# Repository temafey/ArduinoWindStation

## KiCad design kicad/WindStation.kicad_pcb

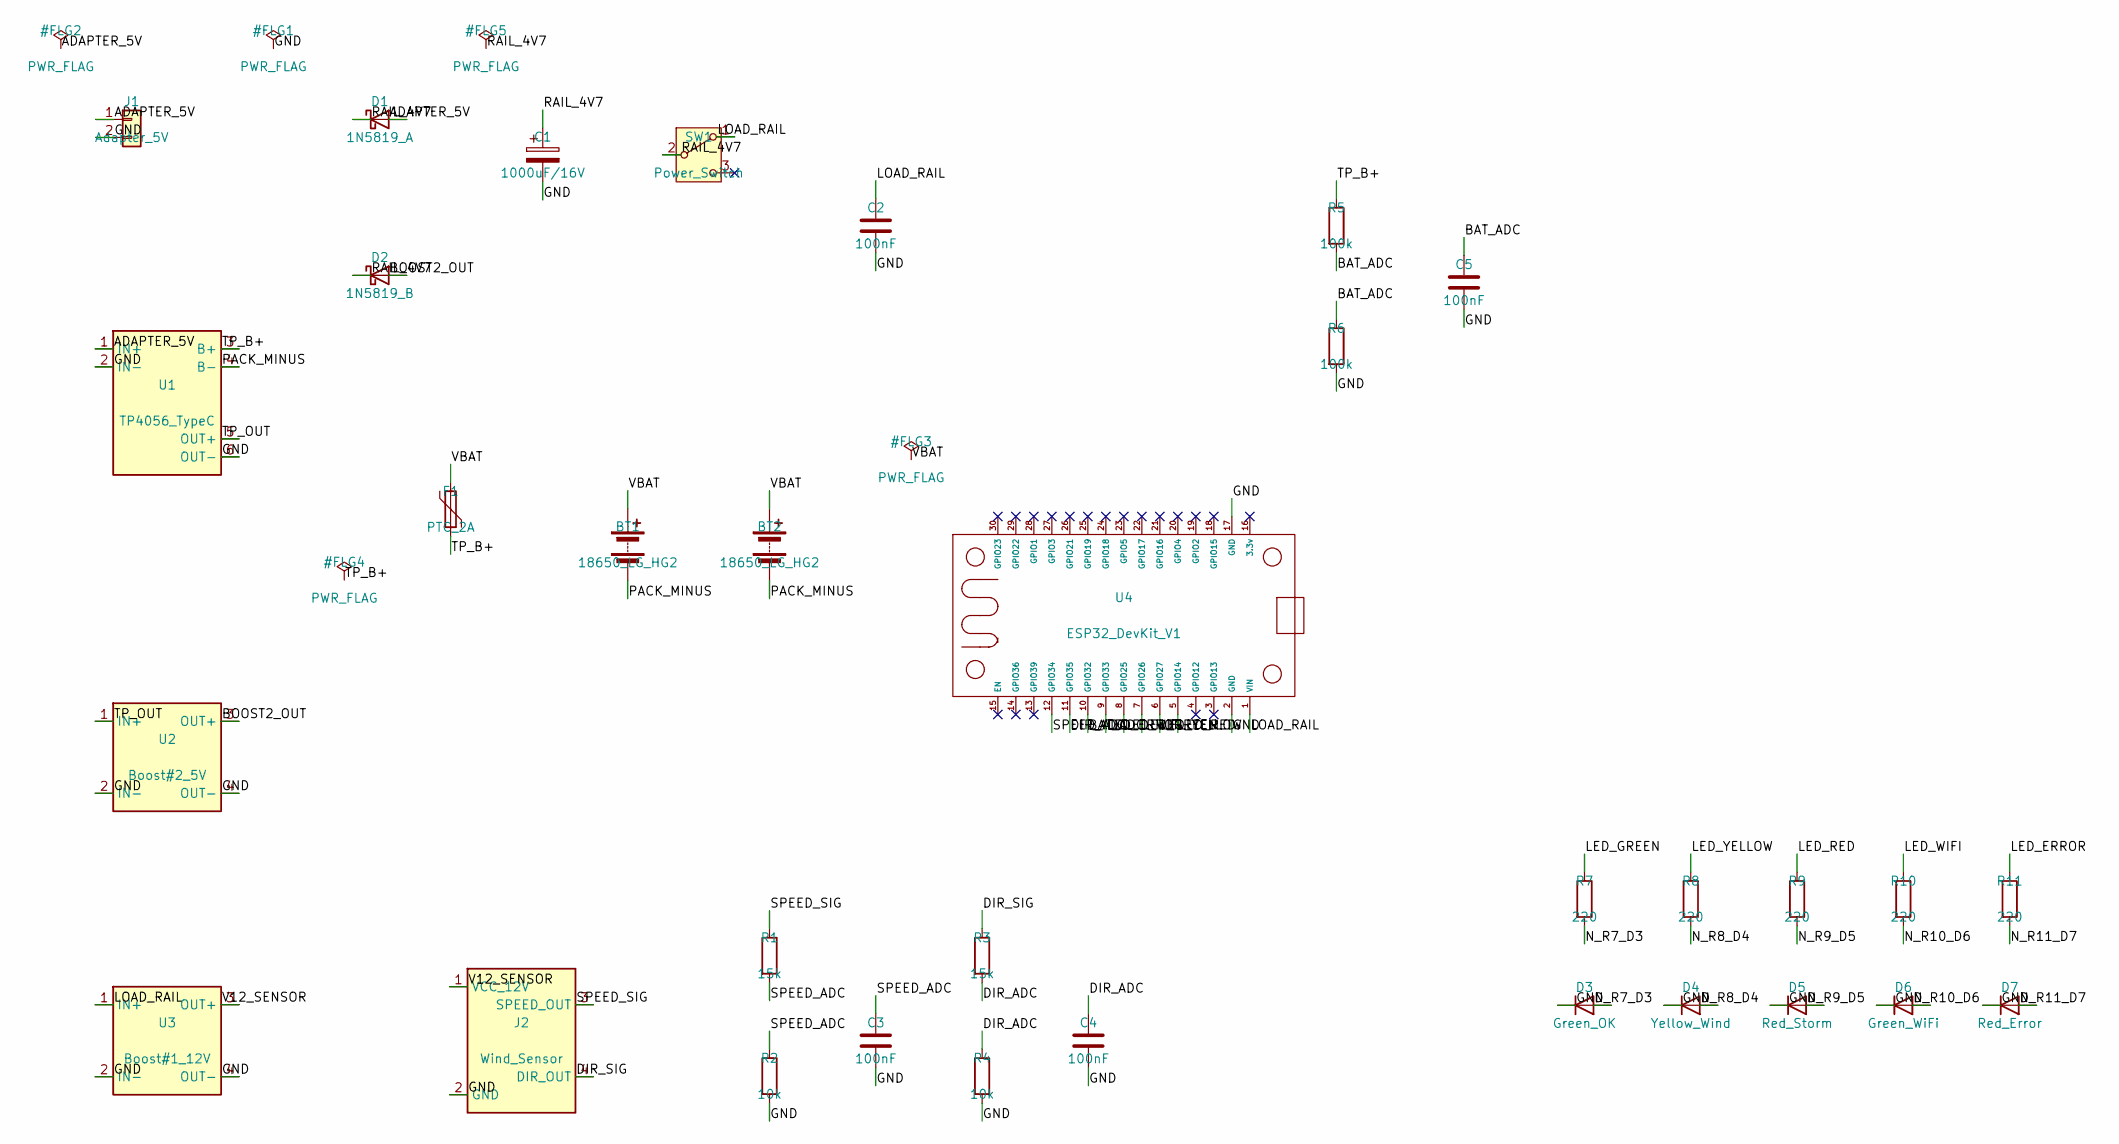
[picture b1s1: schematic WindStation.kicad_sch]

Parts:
BT1, BT2: 18650_LG_HG2; BatteryHolder_Keystone_1042_1x18650
C1: 1000uF/16V; CP_Radial_D10.0mm_P5.00mm
C2, C3, C4, C5: 100nF; C_Disc_D5.0mm_W2.5mm_P5.00mm
D1: 1N5819_A; D_DO-41_SOD81_P10.16mm_Horizontal
D2: 1N5819_B; D_DO-41_SOD81_P10.16mm_Horizontal
D3: Green_OK; LED_D5.0mm
D4: Yellow_Wind; LED_D5.0mm
D5: Red_Storm; LED_D5.0mm
D6: Green_WiFi; LED_D5.0mm
D7: Red_Error; LED_D5.0mm
F1: PTC_2A; Fuse_Bourns_MF-RG400
J1: Adapter_5V; PinHeader_1x02_P2.54mm_Vertical
J2: Wind_Sensor; PinHeader_1x04_P2.54mm_Vertical
R1, R3: 15k; R_Axial_DIN0207_L6.3mm_D2.5mm_P10.16mm_Horizontal
R2, R4: 10k; R_Axial_DIN0207_L6.3mm_D2.5mm_P10.16mm_Horizontal
R5, R6: 100k; R_Axial_DIN0207_L6.3mm_D2.5mm_P10.16mm_Horizontal
R7, R8, R9, R10, R11: 220; R_Axial_DIN0207_L6.3mm_D2.5mm_P10.16mm_Horizontal
SW1: Power_Switch; PinHeader_1x03_P2.54mm_Vertical
U1: TP4056_TypeC; PinHeader_1x06_P2.54mm_Vertical
U2: Boost#2_5V; PinHeader_1x04_P2.54mm_Vertical
U3: Boost#1_12V; PinHeader_1x04_P2.54mm_Vertical
U4: ESP32_DevKit_V1; ESP32_DevKit_V1_30pin

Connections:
/ADAPTER_5V: D1.2 (A), J1.1, U1.1 (IN+)
/BAT_ADC: C5.1, R5.2, R6.1, U4.10 (GPIO32)
/BOOST2_OUT: D2.2 (A), U2.3 (OUT+)
/DIR_ADC: C4.1, R3.2, R4.1, U4.11 (GPIO35)
/DIR_SIG: J2.4 (DIR_OUT), R3.1
/GND: C1.2, C2.2, C3.2, C4.2, C5.2, D3.1 (K), D4.1 (K), D5.1 (K), D6.1 (K), D7.1 (K), J1.2, J2.2 (GND), R2.2, R4.2, R6.2, U1.2 (IN-), U1.6 (OUT-), U2.2 (IN-), U2.4 (OUT-), U3.2 (IN-), U3.4 (OUT-), U4.2 (GND), U4.17 (GND)
/LED_ERROR: R11.1, U4.9 (GPIO33)
/LED_GREEN: R7.1, U4.7 (GPIO26)
/LED_RED: R9.1, U4.5 (GPIO14)
/LED_WIFI: R10.1, U4.8 (GPIO25)
/LED_YELLOW: R8.1, U4.6 (GPIO27)
/LOAD_RAIL: C2.1, SW1.1 (A), U3.1 (IN+), U4.1 (VIN)
/N_R7_D3: D3.2 (A), R7.2
/N_R8_D4: D4.2 (A), R8.2
/N_R9_D5: D5.2 (A), R9.2
/N_R10_D6: D6.2 (A), R10.2
/N_R11_D7: D7.2 (A), R11.2
/PACK_MINUS: BT1.2 (-), BT2.2 (-), U1.4 (B-)
/RAIL_4V7: C1.1, D1.1 (K), D2.1 (K), SW1.2 (B)
/SPEED_ADC: C3.1, R1.2, R2.1, U4.12 (GPIO34)
/SPEED_SIG: J2.3 (SPEED_OUT), R1.1
/TP_B+: F1.2, R5.1, U1.3 (B+)
/TP_OUT: U1.5 (OUT+), U2.1 (IN+)
/V12_SENSOR: J2.1 (VCC_12V), U3.3 (OUT+)
/VBAT: BT1.1 (+), BT2.1 (+), F1.1

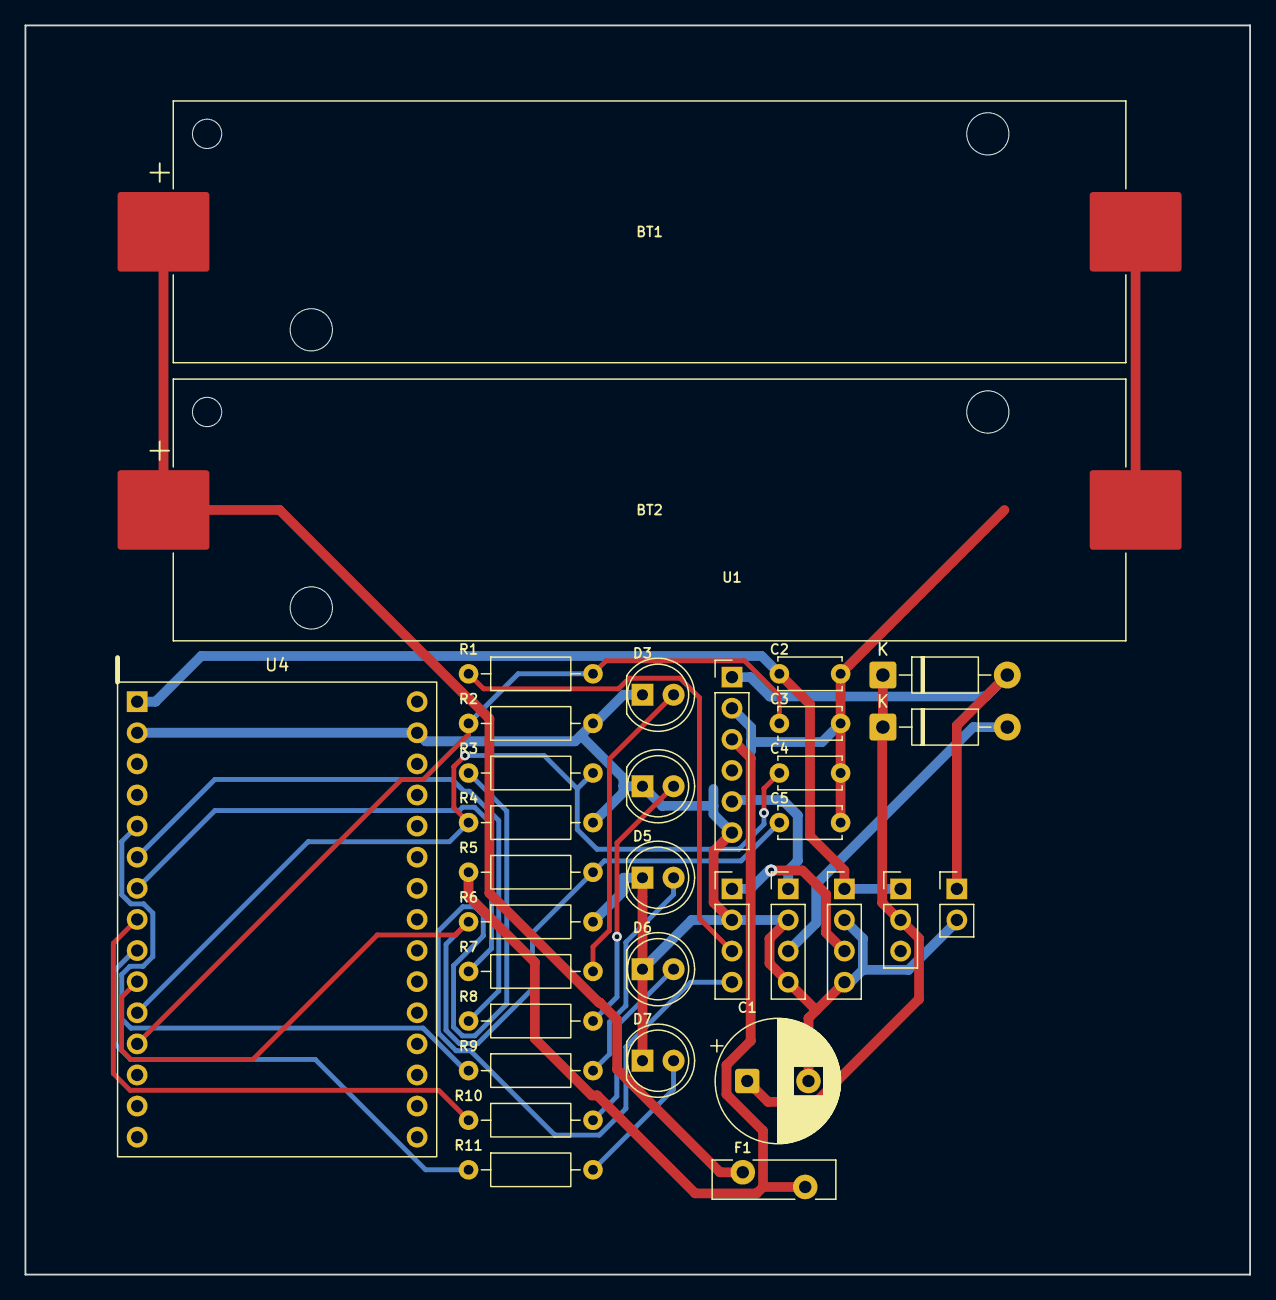
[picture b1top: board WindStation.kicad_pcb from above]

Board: 2 copper layers, 100.0 x 102.0 mm, 33 parts (0 on the bottom side), 25 nets.

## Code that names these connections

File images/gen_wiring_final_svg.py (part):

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                f"{gpio_col}a", f"{anode_col}a", "СВЕТОДИОДЫ", w=2.4, opacity=0.75)

led_wires = (
    led_wire(5, 20, LANE["led14"], bb.LED_R,   "GPIO14 → анод красного") +
    led_wire(6, 28, LANE["led27"], "#d8a017",  "GPIO27 → анод жёлтого") +
    led_wire(7, 36, LANE["led26"], bb.LED_G,   "GPIO26 → анод зелёного") +
    led_wire(8, 44, LANE["led25"], bb.LED_WIFI,"GPIO25 → анод WiFi") +
    led_wire(9, 52, LANE["led33"], "#8d8d8d",  "GPIO33 → анод ошибки"))

# ═══════════════════════════════════════════════════ 6. СИГНАЛЬНЫЕ ПРОВОДА В АЦП
# Подъём через траншею — в промежутке МЕЖДУ колонками, чтобы не путать с узлом.
sig32 = wire([H(48, "g"), (X(48)+8.5, Y("g")), (X(48)+8.5, LANE["g32"]),
              (X(10), LANE["g32"]), H(10, "a")],
             SIG, "узел X (делитель батареи) → GPIO32", "48g", "10a", "АЦП", w=3.0)
sig34 = wire([H(54, "g"), (X(54)+8.5, Y("g")), (X(54)+8.5, LANE["g34"]),
              (X(12), LANE["g34"]), H(12, "a")],
             SIG, "узел 54 (делитель скорости) → GPIO34", "54g", "12a", "АЦП", w=3.0)
sig_lbl = (f'<text x="895" y="418" font-size="9.5" font-weight="700" fill="#c47015">узел X (48g) → 32</text>'
           f'<text x="1074" y="418" font-size="9.5" font-weight="700" fill="#c47015" text-anchor="end">узел 54 (54g) → 34</text>')

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  <text x="{IX+14}" y="{IY+85}" font-size="10.5" fill="#5a4340">не выведены. <tspan font-weight="700">Проверь на плате.</tspan></text>
  <text x="{IX+14}" y="{IY+108}" font-size="11" font-weight="700" fill="#1a1a1a">Если ряд j свободен:</text>
  <text x="{IX+14}" y="{IY+124}" font-size="10.5" fill="#333">STDBY → 19j напрямую. Прошивка без правок.</text>
  <text x="{IX+14}" y="{IY+147}" font-size="11" font-weight="700" fill="#1a1a1a">Если свободен только ряд a → GPIO35:</text>
  <text x="{IX+14}" y="{IY+163}" font-size="10" fill="#666">35 свободен (направления у нового датчика нет),</text>
  <text x="{IX+14}" y="{IY+176}" font-size="10" fill="#666">но он input-only — внутренней подтяжки НЕТ.</text>
  <g stroke-linecap="round" stroke-linejoin="round" fill="none">
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  <text x="{IX+100}" y="{IY+243}" font-size="10.5" font-weight="700" fill="{bb.COPPER}">R7 10k</text>
  <text x="{IX+100}" y="{IY+295}" font-size="10.5" font-weight="700" fill="{bb.COPPER}">R8 20k</text>
  <text x="{IX+256}" y="{IY+204}" font-size="10" font-weight="700" fill="{PLUS}">LOAD</text>
  <text x="{IX+206}" y="{IY+261}" font-size="10" font-weight="700" fill="#c47015">→ GPIO35</text>
  <text x="{IX+206}" y="{IY+284}" font-size="9.5" font-weight="700" fill="#2a7de1">STDBY</text>
  <text x="{IX+136}" y="{IY+326}" font-size="10" fill="#555">«−» рельс</text>
  <text x="{IX+14}" y="{IY+345}" font-size="10" fill="#2e7d32">Покой 4.7×20/30 = <tspan font-weight="700">3.13 В</tspan> (Vih 2.48 В) · ток стока 0.47 мА.</text>
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  <text x="46" y="{NY+87}" font-size="12.5" fill="#c0392b">⚠  <tspan font-weight="700">Колонки 44, 48, 52, 56 живут дважды:</tspan> верхний банк (ряд a) — светодиоды, нижний (f–j) — питание и делители. Это РАЗНЫЕ узлы, траншея их разделяет.</text>
  <text x="46" y="{NY+108}" font-size="12.5" fill="#c0392b">⚠  <tspan font-weight="700">Термоклей поверх поля проводов — нельзя</tspan> (затекает в отверстия по капилляру, гнездо мертво). Модули — на дно, прижимной поролон — в крышку. Силикон только нейтральный.</text>
  <text x="46" y="{NY+129}" font-size="12.5" fill="#2e7d32">✓  Порядок: 1) PPTC · 2) перетыкание по колонкам, по одному проводу · 3) прозвонка 8 мостов · 4) ШИНА 4.6–4.8 В · 5) wiggle-тест каждого провода · 6) закрытие.</text>
  <text x="46" y="{NY+150}" font-size="12.5" fill="#2a6fd1">→  Направление (кол. 16–20) НЕ монтируется: у нового датчика 0–30 м/с этого канала нет. GPIO35 свободен — см. врезку про STDBY.</text>
  <text x="46" y="{NY+168}" font-size="11" fill="#999">Отступление от images/BREADBOARD-STANDARD.md §4.2 (плавные дуги) сделано сознательно: прямые углы здесь — предмет документа.</text>'''

VH = NY + 200
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
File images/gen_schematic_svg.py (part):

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    ], dark=False, tfill=INK))
    o.append(wire([(240, 182), (300, 182)], PLUS))
    o.append(dot(300, 182))
    o.append(netlabel(268, 160, "ADAPTER_5V", PLUS))
    o.append(diode_h(300, 430, 182, "D1 · 1N5819", "катод → шина"))
    o.append(wire([(430, 182), (1090, 182)], PLUS))
    # ответвление на заряд TP4056 IN+
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    o.append(wire([(290, 984), (575, 984), (575, 639)], PURPLE, 3.8))
    o.append(hop(575, 630, PURPLE, 3.8))
    o.append(wire([(575, 621), (575, TPy + TPh)], PURPLE, 3.8))
    o.append(netlabel(700, 984, "PACK_MINUS", PURPLE, anchor="start"))
    o.append(f'<text x="700" y="1008" font-size="11.5" fill="{PURPLE}">'
             f'НЕ на общий GND — иначе DW01A обойдён</text>')

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    o.append(res_v(470, 660, 790, "R6", "100k", lab_side="left"))
    o.append(dot(470, 630, SIG))
    o.append(gnd(470, 790))
    # C5 + оранжевый на GPIO32
    o.append(wire([(470, 630), (1270, 630)], SIG, 3.2))
    o.append(dot(680, 630, SIG))
    o.append(cap_v(680, 630, 700, "C5 100нФ"))
    o.append(gnd(680, 700))
    o.append(wire([(1270, 630), (1270, 400), (1360, 400)], SIG, 3.2))
    o.append(netlabel(950, 630, "BAT_ADC", SIG, volts="ждём 1.99 В и РОВНО"))
    o.append(f'<text x="790" y="612" font-size="11.5" font-weight="700" fill="#c47015">'
             f'узел X → GPIO32</text>')

    # ================= BOOST#2 =================
    o.append(wire([(650, 330), (700, 330)], PLUS))
    o.append(netlabel(675, 282, "TP_OUT", PLUS, volts="ждём 3.9 В"))
    Bx, By, Bw, Bh = 700, 262, 190, 172
    o.append(sch_mod(Bx, By, Bw, Bh, "Mini Boost · MT3608", "→ 5.14 В (задача 02 ✓)", [
        (Bx, 330, "IN+", "left", PLUS, SILK),
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
    # ================= D2 → ШИНА =================
    o.append(wire([(890, 330), (930, 330)], PLUS))
    o.append(netlabel(910, 296, "BOOST2_OUT", PLUS, volts="5.14 В"))
    o.append(diode_h(930, 1090, 330, "D2 · 1N5819", "катод → шина"))
    o.append(wire([(1090, 182), (1090, 330)], PLUS))
    o.append(dot(1090, 182)); o.append(dot(1090, 330))
    o.append(netlabel(1090, 262, "RAIL_4V7", PLUS, volts="4.6–4.8 В"))
    # C1 на шине
    o.append(wire([(1090, 330), (1090, 430)], PLUS))
    o.append(dot(1090, 400))
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    o.append(wire([(1090, 182), (1150, 182)], PLUS))
    o.append(switch_h(1150, 1270, 182, "SW1", "главный выключатель"))
    o.append(wire([(1270, 182), (1420, 182), (1420, 250)], PLUS))
    o.append(netlabel(1330, 160, "LOAD_RAIL", PLUS))
    o.append(dot(1310, 182))
    o.append(wire([(1310, 182), (1310, 250)], PLUS, 3.0))
    o.append(cap_v(1310, 250, 310, "C2 100нФ", polar=False, lab_dx=-24))
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    Ex, Ey, Ew, Eh = 1360, 250, 280, 230
    o.append(sch_mod(Ex, Ey, Ew, Eh, "ESP32 DevKit V1", "DOIT 30-pin · питание по VIN", [
        (1420, Ey, "VIN", "top", PLUS, SILK),
        (Ex, 400, "GPIO32", "left", "#6aa9e0", SILK),
        (1520, Ey + Eh, "GND", "bottom", PAD_GNDp, SILK),
    ], ics=[(1440, 320, 60, "ESP32-WROOM")]))
    o.append(gnd(1520, Ey + Eh + 22))
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
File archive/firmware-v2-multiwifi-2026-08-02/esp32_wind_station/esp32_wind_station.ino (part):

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// ============================================
// Sensor: Polycarbonate 0-5V (speed + direction)
// Signal divider: 15kΩ top + 10kΩ bottom → 5V → 2.0V (linear ADC zone 150 mV … 2.45V)
// Battery divider: 100kΩ + 100kΩ → GPIO32
// LEDs: 5 standard through 220Ω resistors
// Power (diode-OR load sharing):
//   Adapter 5V ─► Schottky_A ─┐
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// Old top-row pins were 26/27/14/25/33. GPIO4/16/17/18 are plain GPIO; GPIO5 is a strapping pin
// (must be HIGH at boot) — an LED-to-GND via 220Ω doesn't hold it low, so it only flickers briefly
// at power-up. Harmless: assigned to WiFi LED, which is meant to be off until WiFi is up anyway.
#define PIN_LED_RED       4   // Red — wind > 15 m/s OR battery 10-30% (blink <10%) (col 5, was 14)
#define PIN_LED_YELLOW   16   // Yellow — wind > 5 m/s OR battery 30-60%            (col 6, was 27)
#define PIN_LED_GREEN    17   // Green — battery > 60% (was "station OK")           (col 7, was 26)
#define PIN_LED_WIFI      5   // Green — WiFi: blink while connecting, solid when up (col 8, was 25; strapping, boot flicker)
#define PIN_LED_ERROR    18   // Red — error (ADC/WiFi)                             (col 9, was 33)

// TP4056 status, open-drain: the IC pulls the pin to GND, so INPUT_PULLUP and LOW=active.
// GPIO13/19 chosen because neither is a strapping pin — an open-drain line held LOW at
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const float SPEED_MAX   = 30.0f;   // m/s at 5V
const float DIR_MAX     = 360.0f;  // degrees at 5V (old sensor only, see HAS_DIRECTION)

// New sensor has no direction channel — GPIO35 hangs unconnected.
// Set to 1 only if the old speed+direction sensor is wired back.
#define HAS_DIRECTION 0

// ESP32 ADC1 @11dB cannot read below ~150 mV: with 0 V in, analogReadMilliVolts()
// bottoms out around this value. Measured on this board at 0 wind: 143-145 mV on
// both GPIO34 and GPIO35 (identical floor on both = proof it is the ADC, not signal).
// Subtracted so calm air reports 0 instead of a phantom 2.2 m/s.
// Re-measure with the sensor still and update if the board changes.
// CONSEQUENCE: real speeds below ~2.2 m/s are indistinguishable from 0 and report 0.
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    ledWifi = wifiOk ? LED_MODE_ON : LED_MODE_BLINK;
  }

  applyLed(PIN_LED_GREEN,  ledGreen);
  applyLed(PIN_LED_YELLOW, ledYellow);
  applyLed(PIN_LED_RED,    ledRed);
  applyLed(PIN_LED_WIFI,   ledWifi);
  digitalWrite(PIN_LED_ERROR, (adcError || !wifiOk) ? HIGH : LOW);
}

const char* ledModeStr(LedMode m) {
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
void startNetworkServices() {
  Serial.printf("WiFi OK: %s  IP: %s\n", WiFi.SSID().c_str(), WiFi.localIP().toString().c_str());
  digitalWrite(PIN_LED_WIFI, HIGH);
  digitalWrite(PIN_LED_ERROR, LOW);

  if (servicesStarted) {
    // Reconnect (possibly a different subnet) — just re-announce mDNS.
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  Serial.begin(115200);
  Serial.println("\n=== Wind Station ===");

  pinMode(PIN_LED_GREEN,  OUTPUT);
  pinMode(PIN_LED_YELLOW, OUTPUT);
  pinMode(PIN_LED_RED,    OUTPUT);
  pinMode(PIN_LED_WIFI,   OUTPUT);
  pinMode(PIN_LED_ERROR,  OUTPUT);

  // TP4056 status lines are open-drain and float when inactive — internal pullup required.
  pinMode(PIN_CHARGE, INPUT_PULLUP);
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  // hardware timer for the whole attempt. digitalRead() on an OUTPUT pin returns the
  // output latch on ESP32, so toggling works.
  wifiBootBlink.attach_ms(250, []() {
    digitalWrite(PIN_LED_WIFI, !digitalRead(PIN_LED_WIFI));
  });

  WiFi.mode(WIFI_STA);
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    WiFi.mode(WIFI_AP_STA);
    WiFi.softAP(setupApName);
    Serial.printf("No known networks — AP '%s' up, dashboard at http://192.168.4.1\n", setupApName);
    digitalWrite(PIN_LED_ERROR, HIGH);
  }

  server.on("/api/data",   HTTP_GET, handleData);
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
